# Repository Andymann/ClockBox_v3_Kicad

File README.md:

# MidiClockBox_v3_Kicad

Different revisions are handled in branches.

Starting with Revision 20251229 we are on USB-C.

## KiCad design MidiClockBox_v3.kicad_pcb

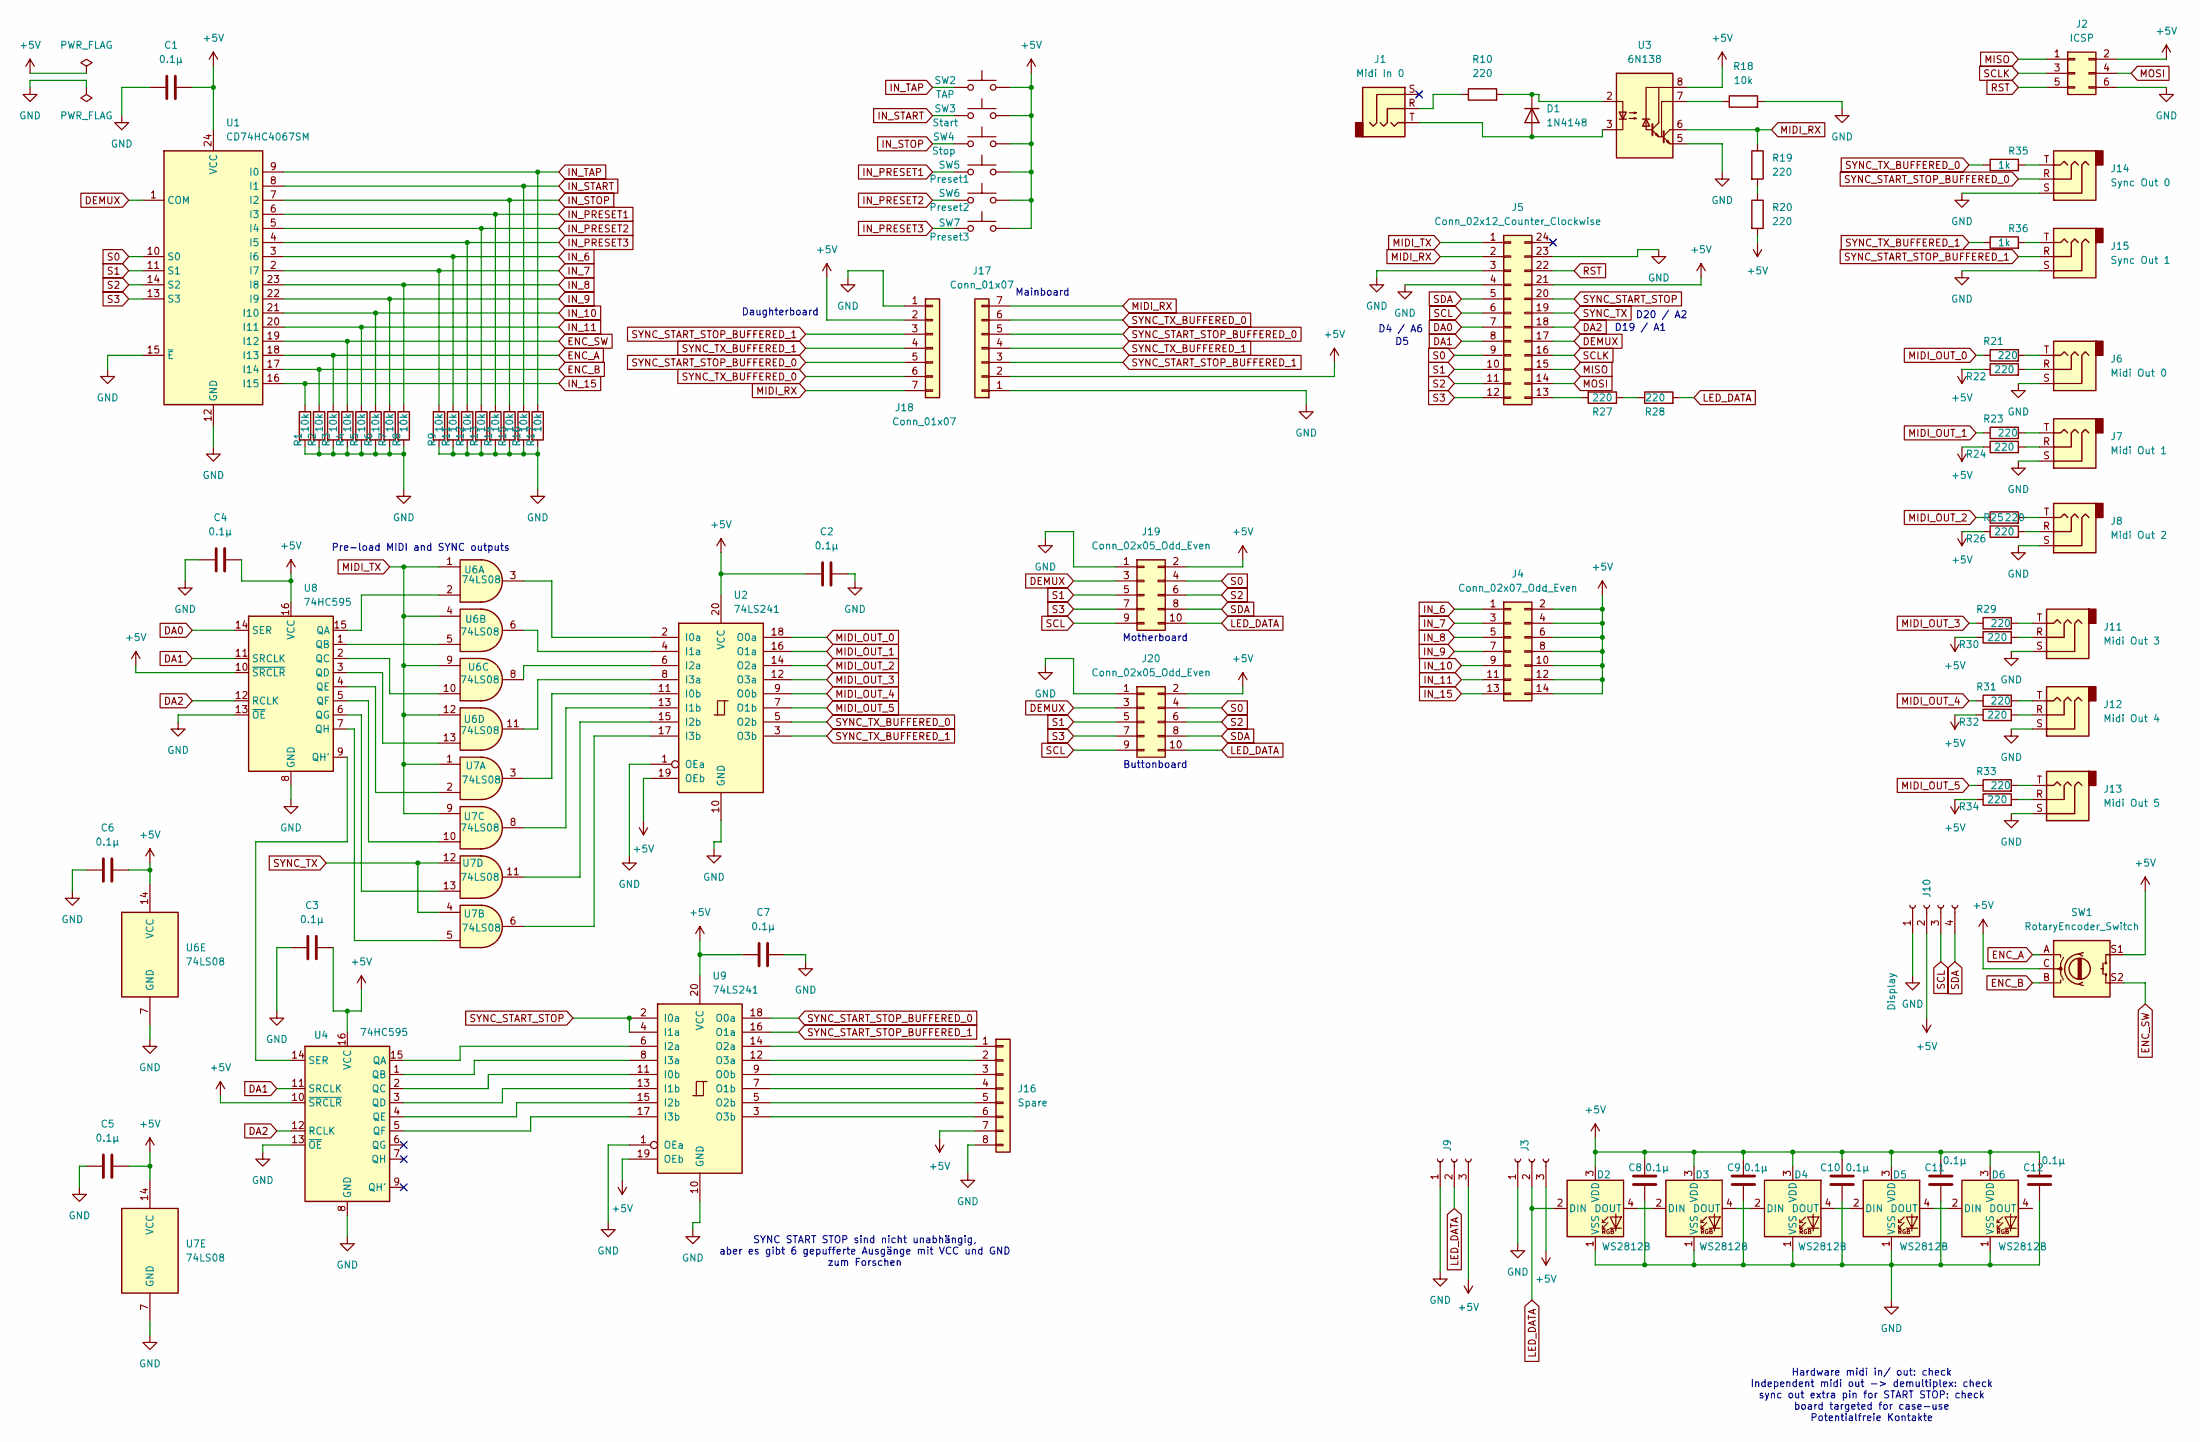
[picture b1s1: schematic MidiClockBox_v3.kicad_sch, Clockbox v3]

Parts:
C1, C2, C3, C4, C5, C6, C7, C8, C9, C10, C11, C12: 0.1µ; C_0603_1608Metric
D1: 1N4148; D_SOD-123
D2, D3, D4, D5, D6: WS2812B; LED_WS2812B_PLCC4_5.0x5.0mm_P3.2mm
J1: Midi In 0; Jack_3.5mm_CUI_SJ-3523-SMT_Horizontal
J2: ICSP; PinHeader_2x03_P2.54mm_Vertical
J3, J9: WS2812; PinHeader_1x03_P2.54mm_Vertical
J4: Conn_02x07_Odd_Even; PinHeader_2x07_P2.54mm_Vertical
J5: Conn_02x12_Counter_Clockwise; DIP-24_W15.24mm
J6: Midi Out 0; Jack_3.5mm_CUI_SJ-3523-SMT_Horizontal
J7: Midi Out 1; Jack_3.5mm_CUI_SJ-3523-SMT_Horizontal
J8: Midi Out 2; Jack_3.5mm_CUI_SJ-3523-SMT_Horizontal
J10: Display; PinHeader_1x04_P2.54mm_Vertical
J11: Midi Out 3; Jack_3.5mm_CUI_SJ-3523-SMT_Horizontal
J12: Midi Out 4; Jack_3.5mm_CUI_SJ-3523-SMT_Horizontal
J13: Midi Out 5; Jack_3.5mm_CUI_SJ-3523-SMT_Horizontal
J14: Sync Out 0; Jack_3.5mm_CUI_SJ-3523-SMT_Horizontal
J15: Sync Out 1; Jack_3.5mm_CUI_SJ-3523-SMT_Horizontal
J16: Spare; PinHeader_1x08_P2.54mm_Vertical
J17, J18: Conn_01x07; PinHeader_1x07_P2.54mm_Vertical
J19, J20: Conn_02x05_Odd_Even; PinHeader_2x05_P2.54mm_Vertical
R1, R2, R3, R4, R5, R6, R7, R8, R9, R11, R12, R13, R14, R15, R16, R17, R18: 10k; R_0603_1608Metric
R10, R19, R20, R21, R22, R23, R24, R25, R26, R27, R28, R29, R30, R31, R32, R33, R34: 220; R_0603_1608Metric
R35, R36: 1k; R_0603_1608Metric
SW1: RotaryEncoder_Switch; RotaryEncoder_Alps_EC11E-Switch_Vertical_H20mm
SW2: TAP; SW_PUSH-12mm_Wuerth-430476085716
SW3: Start; SW_PUSH-12mm_Wuerth-430476085716
SW4: Stop; SW_PUSH-12mm_Wuerth-430476085716
SW5: Preset1; SW_PUSH-12mm_Wuerth-430476085716
SW6: Preset2; SW_PUSH-12mm_Wuerth-430476085716
SW7: Preset3; SW_PUSH-12mm_Wuerth-430476085716
U1: CD74HC4067SM; SOIC-24W_7.5x15.4mm_P1.27mm
U2, U9: 74LS241; SOIC-20W_7.5x12.8mm_P1.27mm
U3: 6N138; SOP-8_6.605x9.655mm_P2.54mm
U4, U8: 74HC595; SO-16_3.9x9.9mm_P1.27mm
U6, U7: 74LS08; SO-14_3.9x8.65mm_P1.27mm

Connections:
+5V: C1.1, C2.1, C3.1, C4.1, C5.1, C6.1, C7.1, C8.1, C9.1, C10.1, C11.1, C12.1, D2.3 (VDD), D3.3 (VDD), D4.3 (VDD), D5.3 (VDD), D6.3 (VDD), J2.2, J3.3, J4.2, J4.4, J4.6, J4.8, J4.10, J4.12, J4.14, J5.21, J9.3, J10.2, J16.7, J17.2, J18.2, J19.2, J20.2, R20.2, R22.1, R24.1, R26.1, R30.1, R32.1, R34.1, SW1.C, SW1.S1, SW2.2, SW3.2, SW4.2, SW5.2, SW6.2, SW7.2, U1.24 (VCC), U2.19 (OEb), U2.20 (VCC), U3.8 (VCC), U4.10 (~SRCLR), U4.16 (VCC), U6.14 (VCC), U7.14 (VCC), U8.10 (~SRCLR), U8.16 (VCC), U9.19 (OEb), U9.20 (VCC)
DA0: J5.7, U8.14 (SER)
DA1: J5.8, U4.11 (SRCLK), U8.11 (SRCLK)
DA2: J5.18, U4.12 (RCLK), U8.12 (RCLK)
DEMUX: J5.17, J19.3, J20.3, U1.1 (COM)
ENC_A: R3.1, SW1.A, U1.18 (I13)
ENC_B: R2.1, SW1.B, U1.17 (I14)
ENC_SW: R4.1, SW1.S2, U1.19 (I12)
GND: C1.2, C2.2, C3.2, C4.2, C5.2, C6.2, C7.2, C8.2, C9.2, C10.2, C11.2, C12.2, D2.1 (VSS), D3.1 (VSS), D4.1 (VSS), D5.1 (VSS), D6.1 (VSS), J2.6, J3.1, J5.3, J5.4, J5.23, J6.S, J7.S, J8.S, J9.1, J10.1, J11.S, J12.S, J13.S, J14.S, J15.S, J16.8, J17.1, J18.1, J19.1, J20.1, R1.2, R2.2, R3.2, R4.2, R5.2, R6.2, R7.2, R8.2, R9.2, R11.2, R12.2, R13.2, R14.2, R15.2, R16.2, R17.2, R18.2, U1.12 (GND), U1.15 (~E), U2.1 (OEa), U2.10 (GND), U3.5 (GND), U4.8 (GND), U4.13 (~OE), U6.7 (GND), U7.7 (GND), U8.8 (GND), U8.13 (~OE), U9.1 (OEa), U9.10 (GND)
IN_6: J4.1, R11.1, U1.3 (I6)
IN_7: J4.3, R9.1, U1.2 (I7)
IN_8: J4.5, R8.1, U1.23 (I8)
IN_9: J4.7, R7.1, U1.22 (I9)
IN_10: J4.9, R6.1, U1.21 (I10)
IN_11: J4.11, R5.1, U1.20 (I11)
IN_15: J4.13, R1.1, U1.16 (I15)
IN_PRESET1: R14.1, SW5.1, U1.6 (I3)
IN_PRESET2: R13.1, SW6.1, U1.5 (I4)
IN_PRESET3: R12.1, SW7.1, U1.4 (I5)
IN_START: R16.1, SW3.1, U1.8 (I1)
IN_STOP: R15.1, SW4.1, U1.7 (I2)
IN_TAP: R17.1, SW2.1, U1.9 (I0)
LED_DATA: D2.2 (DIN), J3.2, J9.2, J19.10, J20.10, R28.2
MIDI_OUT_0: R21.1, U2.18 (O0a)
MIDI_OUT_1: R23.1, U2.16 (O1a)
MIDI_OUT_2: R25.1, U2.14 (O2a)
MIDI_OUT_3: R29.1, U2.12 (O3a)
MIDI_OUT_4: R31.1, U2.9 (O0b)
MIDI_OUT_5: R33.1, U2.7 (O1b)
MIDI_RX: J5.2, J17.7, J18.7, R19.1, U3.6 (VO2)
MIDI_TX: J5.1, U6.1, U6.4, U6.9, U6.12, U7.1, U7.9
MISO: J2.1, J5.15
MOSI: J2.4, J5.14
unnamed: D1.2 (A), J1.T, U3.3 (C2)
unnamed: D1.1 (K), R10.2, U3.2 (C1)
unnamed: D2.4 (DOUT), D3.2 (DIN)
unnamed: D3.4 (DOUT), D4.2 (DIN)
unnamed: D4.4 (DOUT), D5.2 (DIN)
unnamed: D5.4 (DOUT), D6.2 (DIN)
unnamed: J1.R, R10.1
unnamed: J5.13, R27.2
unnamed: J6.R, R22.2
unnamed: J6.T, R21.2
unnamed: J7.R, R24.2
unnamed: J7.T, R23.2
unnamed: J8.R, R26.2
unnamed: J8.T, R25.2
unnamed: J11.R, R30.2
unnamed: J11.T, R29.2
unnamed: J12.R, R32.2
unnamed: J12.T, R31.2
unnamed: J13.R, R34.2
unnamed: J13.T, R33.2
unnamed: J14.T, R35.2
unnamed: J15.T, R36.2
unnamed: J16.1, U9.14 (O2a)
unnamed: J16.2, U9.12 (O3a)
unnamed: J16.3, U9.9 (O0b)
unnamed: J16.4, U9.7 (O1b)
unnamed: J16.5, U9.5 (O2b)
unnamed: J16.6, U9.3 (O3b)
unnamed: R19.2, R20.1
unnamed: R27.1, R28.1
unnamed: U2.2 (I0a), U6.3
unnamed: U2.11 (I0b), U7.3
unnamed: U2.4 (I1a), U6.6
unnamed: U2.13 (I1b), U7.8
unnamed: U2.6 (I2a), U6.8
unnamed: U2.15 (I2b), U7.11
unnamed: U2.8 (I3a), U6.11
unnamed: U2.17 (I3b), U7.6
unnamed: R18.1, U3.7 (VO1)
unnamed: U4.15 (QA), U9.6 (I2a)
unnamed: U4.1 (QB), U9.8 (I3a)
unnamed: U4.2 (QC), U9.11 (I0b)
unnamed: U4.3 (QD), U9.13 (I1b)
unnamed: U4.4 (QE), U9.15 (I2b)
unnamed: U4.5 (QF), U9.17 (I3b)
unnamed: U4.14 (SER), U8.9 (QH')
unnamed: U6.2, U8.15 (QA)
unnamed: U6.5, U8.1 (QB)
unnamed: U6.10, U8.2 (QC)
unnamed: U6.13, U8.3 (QD)
unnamed: U7.2, U8.4 (QE)
unnamed: U7.10, U8.5 (QF)
unnamed: U7.13, U8.6 (QG)
unnamed: U7.5, U8.7 (QH)
RST: J2.5, J5.22
S0: J5.9, J19.4, J20.4, U1.10 (S0)
S1: J5.10, J19.5, J20.5, U1.11 (S1)
S2: J5.11, J19.6, J20.6, U1.14 (S2)
S3: J5.12, J19.7, J20.7, U1.13 (S3)
SCL: J5.6, J10.3, J19.9, J20.9
SCLK: J2.3, J5.16
SDA: J5.5, J10.4, J19.8, J20.8
SYNC_START_STOP: J5.20, U9.2 (I0a), U9.4 (I1a)
SYNC_START_STOP_BUFFERED_0: J14.R, J17.5, J18.5, U9.18 (O0a)
SYNC_START_STOP_BUFFERED_1: J15.R, J17.3, J18.3, U9.16 (O1a)
SYNC_TX: J5.19, U7.4, U7.12
SYNC_TX_BUFFERED_0: J17.6, J18.6, R35.1, U2.5 (O2b)
SYNC_TX_BUFFERED_1: J17.4, J18.4, R36.1, U2.3 (O3b)

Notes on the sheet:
Daughterboard
Hardware midi in/ out: check Independent midi out -> demultiplex: check sync out extra pin for START STOP: check board targeted for case-use Potentialfreie Kontakte
Mainboard
Buttonboard
SYNC START STOP sind nicht unabhängig, aber es gibt 6 gepufferte Ausgänge mit VCC und GND zum Forschen
D20 / A2
Motherboard
Pre-load MIDI and SYNC outputs
D19 / A1
D4 / A6

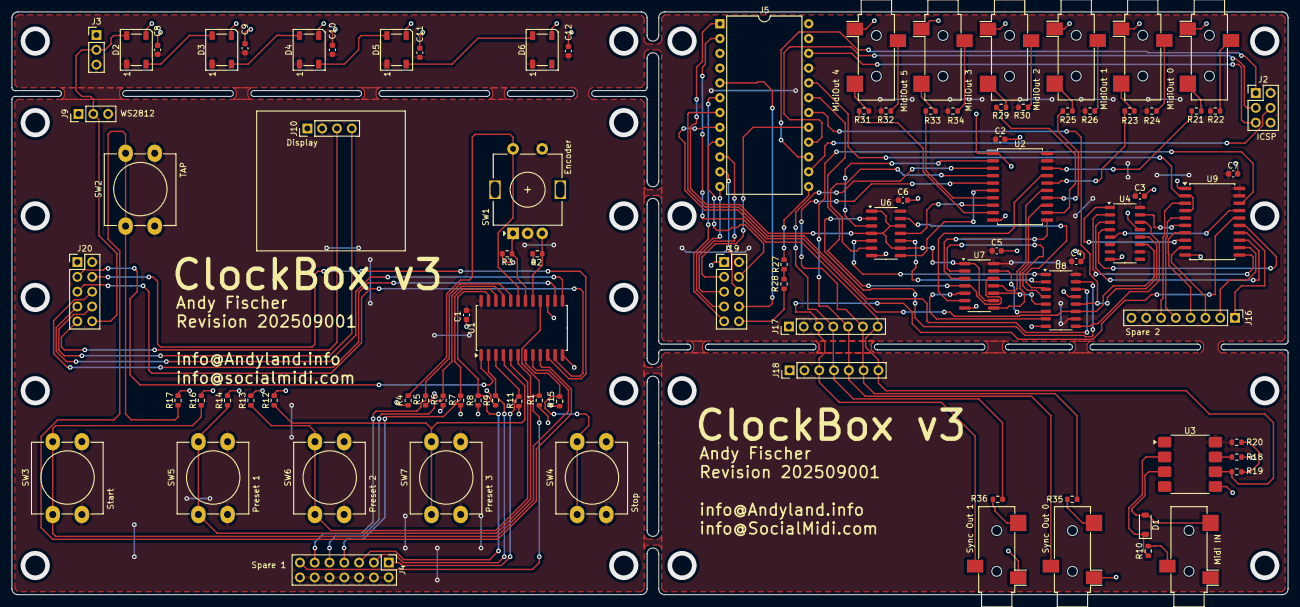
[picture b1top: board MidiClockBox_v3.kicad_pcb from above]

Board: 2 copper layers, 219.0 x 100.0 mm, 89 parts (0 on the bottom side), 101 nets.

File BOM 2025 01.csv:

Reference;Quantity;Manufacturer;MFG Part#;Footprint;Description
C1,C2,C3,C4,C5,C6,C7,C8,C9,C10,C11,C12;12;Kemet;C0603C104K1RACTU;C_0603_1608Metric;0.1µ
D1;1;Diodes Incorporated;1N4148W-7-F;SOD123;1N4148W
D2,D3,D4,D5,D6;5;Adafruit Industries LLC;1655;LED_SMD:LED_WS2812B_PLCC4_5.0x5.0mm_P3.2mm;WS2812b, ADDRESS LED DISC SERIAL RGB 1=10
J1,J6,J7,J8,J11,J12,J13,J14,J15;9;CUI Devices;SJ-3523-SMT-TR;Jack_3.5mm_CUI_SJ-3523-SMT_Horizontal;
R1,R2,R3,R4,R5,R6,R7,R8,R9,R11,R12,R13,R14,R15,R16,R17,R18;17;Vishay/ Dale;CRCW060310K0JNEAIF;R_0603_1608Metric;10k
R10,R19,R20,R21,R22,R23,R24,R25,R26,R27,R28,R29,R30,R31,R32,R33,R34;17;Vishay/ Dale;CRCW0603220RJNEAHP;R_0603_1608Metric;220 Ohm
R35,R36;2;Vishay/ Dale;CRCW06031K00DHEBP;R_0603_1608Metric;10k
U3;1;Broadcom/ Avago;6N138-300E;SOP-8_6.62x9.15mm_P2.54mm;6N138
U1;1;Texas Instruments;CD74HC4067M96;SOIC-24W_7.5x15.4mm_P1.27mm;CD74HC4067SM
U2,U9;2;Texas Instruments;SN74LS241NSR;Package_SO:SOIC-20W_7.5x12.8mm_P1.27mm;74ls241
U4,U8;2;Texas Instruments;SN74HC595NSR;Package_SO:SO-16_3.9x9.9mm_P1.27mm;74hc595
U6,U7;2;Texas Instruments;SN74LS08DRE4;Package_SO:SO-14_3.9x8.65mm_P1.27mm;74ls08
J2,J3,J4,J5,J9,J10,J16,J17,J18,J19,J20;;;;;not used
SW1,SW2,SW3,SW4,SW5,SW6,SW7;;;;;not used

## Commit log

2024-01-24 add circuit board design
2024-01-27 refine circuitboard layout
2024-01-27 switch resistor network for SMD parts
2024-01-29 switch SMD components form 0201-0603 to 0603-1608
2024-02-19 add centroid archive
2024-03-12 move logo to front silkscreen
2024-03-12 add info to README.md
2024-03-12 add info
2024-10-12 Add info about legacy branch
2024-10-12 add branch info
2024-11-03 swtich to hardware serial
2024-11-04 add comments for stuff 2do
2024-11-29 add stuff
2024-11-29 add parts to pcb
2024-12-05 add edge cuts
2024-12-08 change layout
2024-12-25 increase size to something useful
2024-12-25 move breakable edge of main part
2025-01-09 add recent changes
2025-01-13 add breakout connectors for sync-out and midi-in
2025-01-15 pcb looks complete
2025-01-15 add BOM
2025-01-15 add silkscreen text
2025-01-21 fix BOM
2025-07-26 change silkscreen info's size
2025-09-22 fix Adafruit LED pinout and BOM
2025-12-27 add title and revision to schema and pcb
2026-01-01 move to usb-c
